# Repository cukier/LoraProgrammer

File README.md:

# LoraProgrammer

Firmware ESP32 (ESP-IDF) para programar e configurar módulos de rádio LoRa, expondo a configuração através de um servidor HTTP em Wi-Fi (SoftAP/STA), acessível também via mDNS (`http://<hostname>.local/`).

Dois rádios são suportados; apenas um é compilado por build, escolhido no `menuconfig`:

| Rádio | Interface | Como funciona |
|---|---|---|
| **RF1276 / YL_800IL** — [AppConWireless](https://www.appconwireless.com/) (*padrão*) | UART | Módulo com MCU próprio. O ESP32 lê/escreve os parâmetros (baudrate, paridade, frequência, spreading factor, modo, largura de banda, ID, Net ID, potência) pelo protocolo de comandos com header `0xAF`; os dados de payload são transparentes (bytes crus na mesma UART). |
| **LoRa127X-C1 / SX1276** — [NiceRF](https://www.nicerf.com/) | SPI nativa | Modem SX1276 controlado diretamente pelo ESP32 (componente `dernasherbrezon/sx127x`). Não tem memória de configuração: "programar" significa aplicar os parâmetros (frequência, largura de banda, SF, coding rate, sync word, preâmbulo, potência, CRC) a cada boot e em runtime via `POST /lora`. |

### Selecionar o rádio

```bash
cd src
idf.py menuconfig   # → "KLORA Configuration" → "LoRa radio module"
idf.py build
```

Sem `menuconfig`, o build usa o RF1276 (`CONFIG_KLORA_RADIO_RF1276=y`). Os pinos
(UART ou SPI) e os parâmetros de rádio ficam no mesmo menu, e são aplicados no
boot. A escolha do rádio também está exposta como variável de CMake, então o
`main/CMakeLists.txt` compila só o back end selecionado (`kuart.c` + `RF1216.c`
ou `klora_sx127x.c`).

### API HTTP (igual para os dois rádios)

| Método | Rota | Descrição |
|---|---|---|
| `GET`  | `/info`      | RAM livre, versão do firmware, IP, uptime, hora local |
| `GET`  | `/lora`      | Configuração atual do rádio (JSON) |
| `POST` | `/lora`      | Aplica/grava parâmetros do rádio (corpo JSON, qualquer subconjunto) |
| `GET`  | `/lora/rxtx` | Hex dump do último pacote recebido pelo ar |
| `POST` | `/lora/rxtx` | Transmite um payload — corpo JSON `{"message": "..."}` |
| `POST` | `/ota`       | Atualização de firmware |
| `POST` | `/reboot`    | Reinicia o dispositivo após 5 s |

O formato do JSON de `/lora` difere entre os rádios (parâmetros distintos), mas a
saída do `GET` sempre volta a valer como corpo do `POST` para o mesmo back end.

## Estrutura do repositório

```
src/        Firmware ESP-IDF (projeto CMake)
  main/     Componente principal (código-fonte)
sch/        Projeto de hardware em KiCad
.github/    Workflows de CI (build do firmware e exports do KiCad)
```

## Firmware

Projeto ESP-IDF padrão. Para compilar:

```bash
cd src
idf.py build
idf.py -p <PORT> flash monitor
```

O CI (`.github/workflows/firmware.yml`) compila o firmware a cada push/PR em `src/**` e publica os binários (`.bin`, `bootloader.bin`, `partition-table.bin`) como artifact.

## Hardware

Esquemático e PCB em `sch/` (KiCad 9). O CI (`.github/workflows/hardware.yml`) exporta Gerbers, drill files e BOM a cada push/PR em `sch/**`.

## Configuração

`radio.json` documenta o formato dos parâmetros de rádio (back end RF1276) expostos pela API HTTP do firmware.

## Licença

MIT — veja [LICENSE](LICENSE).

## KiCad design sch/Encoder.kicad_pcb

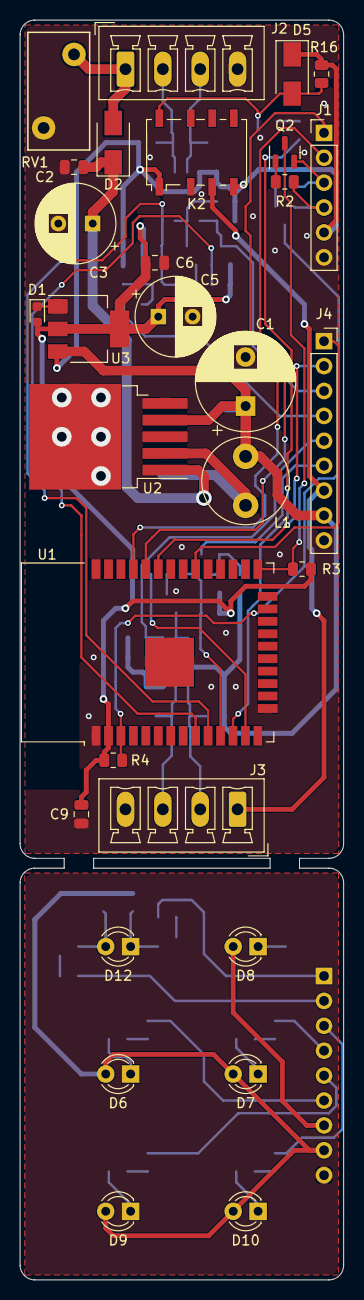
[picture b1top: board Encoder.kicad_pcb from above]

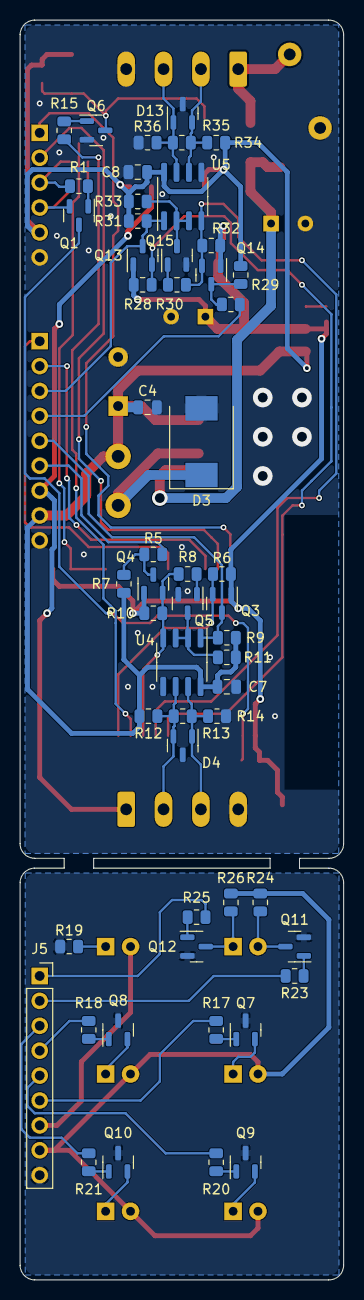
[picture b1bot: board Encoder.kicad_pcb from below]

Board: 2 copper layers, 33.0 x 128.5 mm, 84 parts (54 on the bottom side), 60 nets.

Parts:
C1: 1000uF; CP_Radial_D10.0mm_P5.00mm
C2, C4, C6, C7, C8, C9: 100nF; C_0805_2012Metric
C3, C5: 470uF; CP_Radial_D8.0mm_P3.50mm
D1: ESD9B3.3ST5G; D_0603_1608Metric
D2, D5: US1M; D_SMA
D3: SS35; D_SMC
D4, D13: SM712; SOT-23
D6: TX1; LED_D3.0mm
D7: TX2; LED_D3.0mm
D8: ENC; LED_D3.0mm
D9, D10: RX2; LED_D3.0mm
D12: HEART_BEAT; LED_D3.0mm
J1: PROG; PinHeader_1x06_P2.54mm_Vertical
J2: PWR; PhoenixContact_MCV_1,5_4-G-3.81_1x04_P3.81mm_Vertical
J3: ENC; PhoenixContact_MCV_1,5_4-G-3.81_1x04_P3.81mm_Vertical
J4: CON_I; PinSocket_1x09_P2.54mm_Vertical
J5: CON_O; PinSocket_1x09_P2.54mm_Vertical
K2: G6K-2; Relay_DPDT_Omron_G6K-2F-Y
L1: 100uH; L_Radial_D8.7mm_P5.00mm_Fastron_07HCP
Q1, Q2, Q5, Q15: MMBT2222ALT1G; SOT-23
Q3, Q4, Q13, Q14: MMBF170; SOT-23
Q6, Q11, Q12: BC817; SOT-23
Q7, Q8, Q9, Q10: BC807; SOT-23
R1, R2, R3, R4, R5, R6, R7, R9, R10, R11, R16, R17, R18, R20, R21, R23, R25, R27, R28, R29, R31, R32, R33: 10k; R_0805_2012Metric
R8, R15, R19, R24, R26, R30: 1k; R_0805_2012Metric
R12, R14, R34, R36: 560R; R_0805_2012Metric
R13, R35: 120R; R_0805_2012Metric
RV1: 10D390K; RV_Disc_D12mm_W6.3mm_P7.5mm
U1: ESP32-WROOM-32
U2: LM2596S-5; TO-263-5_TabPin3
U3: AP1117-33; SOT-223-3_TabPin2
U4, U5: SP3485EN; SOIC-8_3.9x4.9mm_P1.27mm

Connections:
+3V3: C5.1, C6.1, C9.1, D1.2 (A2), Q3.1 (G), Q4.1 (G), Q13.1 (G), Q14.1 (G), R3.1, R4.1, R6.2, R10.2, R28.2, R32.2, U1.2 (VDD), U3.2 (VO)
+5V: C1.1, C4.1, C7.1, C8.1, D5.1 (K), J1.5, J4.8, K2.1, K2.4, L1.2, R7.2, R9.2, R11.2, R12.2, R16.2, R29.2, R31.2, R33.2, R34.2, U2.4 (FB), U3.3 (VI), U4.8 (VCC), U5.8 (VCC)
+5VA: D6.2 (A), D7.2 (A), D9.2 (A), D10.2 (A), J5.8, R24.2, R26.2
+24V: D2.2 (A), J2.1, RV1.1
/A_ENC: D4.2 (A2), J3.2, R12.1, R13.2, U4.6 (A)
/A_PLC: D13.2 (A2), J2.2, R34.1, R35.2, U5.6 (A)
/B_ENC: D4.1 (A1), J3.3, R13.1, R14.2, U4.7 (B)
/B_PLC: D13.1 (A1), J2.3, R35.1, R36.2, U5.7 (B)
/Core/BOOT: Q2.3 (C), R3.2, U1.25 (IO0)
/Core/DTR: J1.3, Q2.2 (E), R1.2
/Core/RTS: J1.4, Q1.2 (E), R2.2
/Core/RX: J1.2, U1.34 (RXD0/IO3)
/Core/TX: J1.1, U1.35 (TXD0/IO1)
/Core/~RESET: Q1.3 (C), R4.2, U1.3 (EN)
/ENC_OK: J3.1, J4.7, K2.3
/EN_ENC: R15.2, U1.12 (IO27)
/HB_1: J4.2, U1.33 (IO21)
/HB_2: J4.1, U1.30 (IO18)
/IHM/ENC_OK: D8.2 (A), J5.7
/IHM/HB1: J5.2, R23.2
/IHM/HB2: J5.1, R25.2
/IHM/RX1: J5.5, R20.2
/IHM/RX2: J5.3, R21.2
/IHM/TX1: J5.6, R17.2
/IHM/TX2: J5.4, R18.2
/RXO_ENC: J4.5, Q3.3 (D), R9.1, U4.1 (RO)
/RXO_PLC: J4.3, Q13.3 (D), R31.1, U5.1 (RO)
/RX_ENC: Q3.2 (S), R6.1, U1.13 (IO14)
/RX_PLC: Q13.2 (S), R28.1, U1.9 (IO33)
/TXO_ENC: J4.6, R5.2
/TXO_PLC: J4.4, R27.2
/TX_ENC: Q4.2 (S), R8.2, R10.1, U1.11 (IO26), U4.4 (DI)
/TX_PLC: Q14.2 (S), R30.2, R32.1, U1.10 (IO25), U5.4 (DI)
/Transdutor Enc/~RE/DE: Q5.3 (C), R11.1, U4.2 (~RE), U4.3 (DE)
/Transdutor PLC/~RE/DE: Q15.3 (C), R33.1, U5.2 (~RE), U5.3 (DE)
GND: C1.2, C2.2, C3.2, C4.2, C5.2, C6.2, C7.2, C8.2, C9.2, D1.1 (A1), D3.2 (A), D4.3 (common), D13.3 (common), J1.6, J2.4, J3.4, J4.9, Q5.2 (E), Q6.2 (E), Q15.2 (E), R14.1, R36.1, RV1.2, U1.1 (GND), U1.15 (GND), U1.38 (GND), U1.39 (GND), U2.3 (GND), U2.5 (~ON/OFF), U3.1 (GND), U4.5 (GND), U5.5 (GND)
GNDA: J5.9, Q7.3 (C), Q8.3 (C), Q9.3 (C), Q10.3 (C), Q11.2 (E), Q12.2 (E), R19.1
unnamed: C2.1, C3.1, D2.1 (K), U2.1 (VIN)
unnamed: D3.1 (K), L1.1, U2.2 (OUT)
unnamed: D5.2 (A), K2.8, Q6.3 (C), R16.1
unnamed: D6.1 (K), Q7.2 (E)
unnamed: D7.1 (K), Q8.2 (E)
unnamed: D8.1 (K), R19.2
unnamed: D9.1 (K), Q9.2 (E)
unnamed: D10.1 (K), Q10.2 (E)
unnamed: D12.2 (A), Q11.3 (C), R24.1
unnamed: D12.1 (K), Q12.3 (C), R26.1
unnamed: Q1.1 (B), R1.1
unnamed: Q2.1 (B), R2.1
unnamed: Q4.3 (D), R5.1, R7.1
unnamed: Q5.1 (B), R8.1
unnamed: Q6.1 (B), R15.1
unnamed: Q7.1 (B), R17.1
unnamed: Q8.1 (B), R18.1
unnamed: Q9.1 (B), R20.1
unnamed: Q10.1 (B), R21.1
unnamed: Q11.1 (B), R23.1
unnamed: Q12.1 (B), R25.1
unnamed: Q14.3 (D), R27.1, R29.1
unnamed: Q15.1 (B), R30.1
